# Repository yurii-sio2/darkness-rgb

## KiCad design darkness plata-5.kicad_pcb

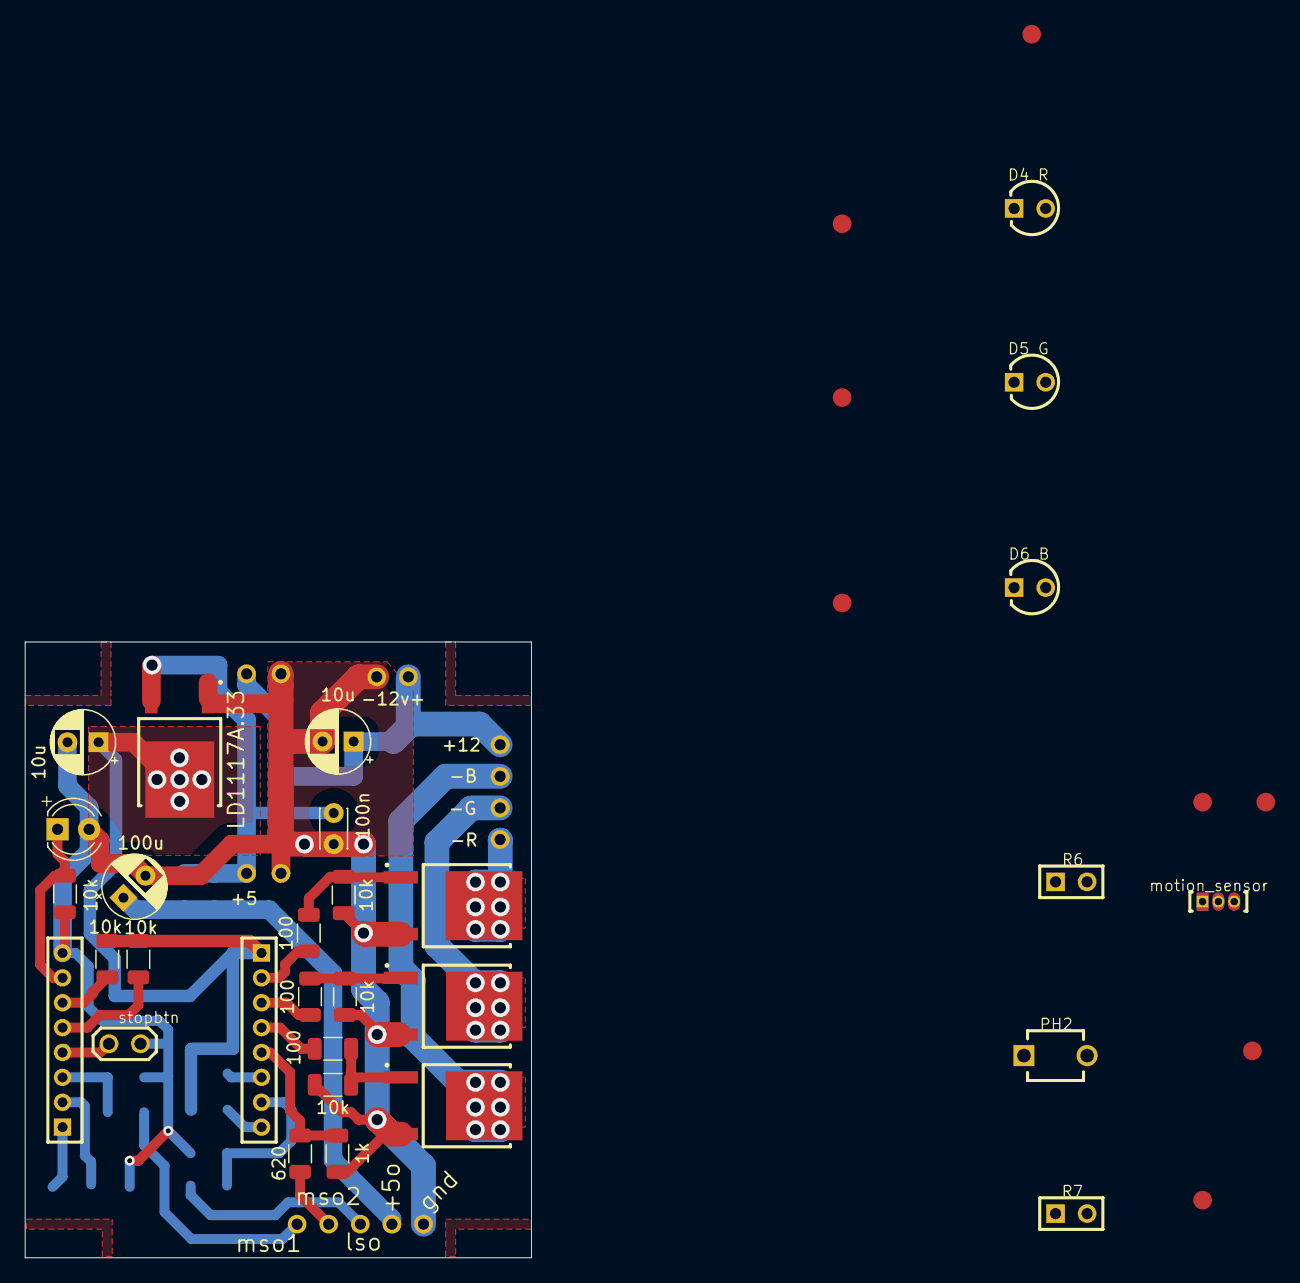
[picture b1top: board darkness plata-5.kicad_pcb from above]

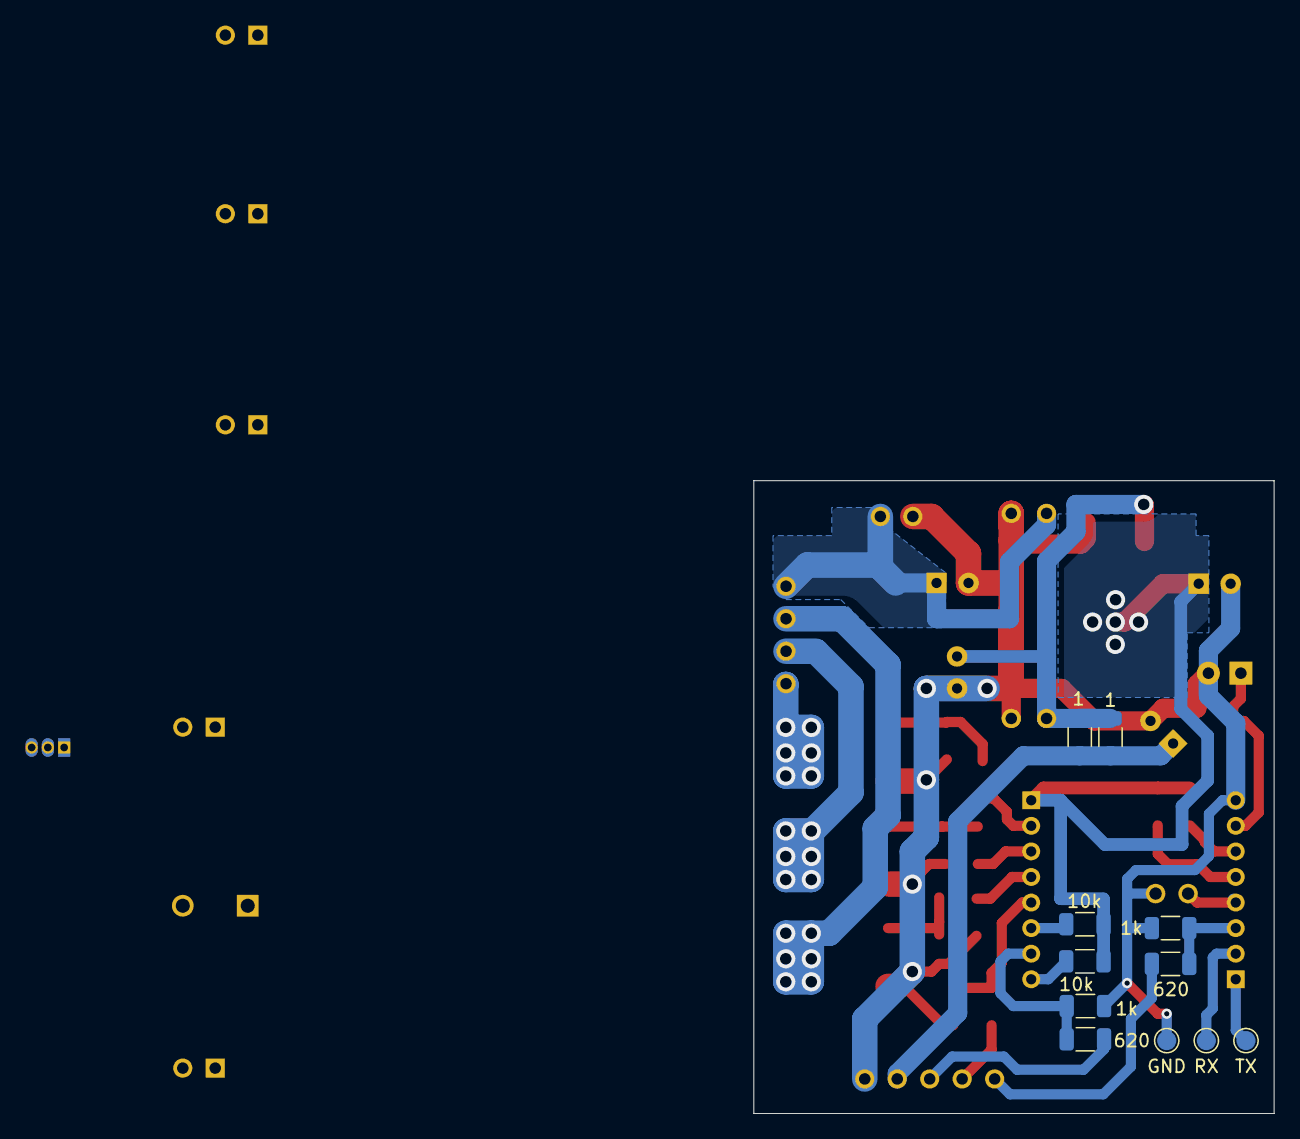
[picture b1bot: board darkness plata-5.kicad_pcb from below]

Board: 2 copper layers, 40.7 x 49.5 mm, 64 parts (11 on the bottom side), 35 nets.

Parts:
100n: 100n; C_Disc_D3.0mm_W2.0mm_P2.50mm
+3.3, +12in0: ONE CONNECTOR; One_Contact_Pin_+3.3
+12: ONE CONNECTOR; One_Contact_Pin
+12stab0: ONE CONNECTOR; One_Contact_Pin_+12stab
+rgb0: ONE CONNECTOR; One_Contact_Pin
-3.3: PAD; One_Contact_Pin_-3.3
-12: ONE CONNECTOR; One_Contact_Pin
-12in0: PAD; Pad_-12in
-B0: ONE CONNECTOR; One_Contact_Pin_-B
-G0: ONE CONNECTOR; One_Contact_Pin_-B
-R0: ONE CONNECTOR; One_Contact_Pin_-B
C1, C2: 10u; CP_Radial_D5.0mm_P2.50mm
C2#2: 100u; CP_Radial_D5.0mm_P2.50mm
D1: 4mm Round; LED_D4.0mm
D4_R0, D5_G0, D6_B0: QEC112
GND: GND; TestPoint_Pad_D1.5mm
J1, J2: 51015-0800
LIGHT_SENSOR0: ONE CONNECTOR; One_Contact_Pin_motion+3.1
PH2: 1k-150k; BP104F
Q1, Q2, Q3: P0903; TO252_50N024-09P
Q4: LD1117A.33; TO252_50N024-09P
R6: 2k; HDR-1x2
R7: 30k; HDR-1x2
R8, R9, R10#5, R11, R12, R13, R15, R17: 10k; R_1206_3216Metric
R10, R10#3, R10#6: 620; R_1206_3216Metric
R10#2, R10#4, R10#7: 1k; R_1206_3216Metric
R14, R16, R18: 100; R_1206_3216Metric
R19, R19#2: 1; R_1206_3216Metric
RX: RX; TestPoint_Pad_D1.5mm
TX: TX; TestPoint_Pad_D1.5mm
from_BLUE-0: ONE CONNECTOR; One_Contact_Pin_+12stab
from_GREEN-0: ONE CONNECTOR; One_Contact_Pin_+12stab
from_RED-0: ONE CONNECTOR; One_Contact_Pin_+12stab
motion+3.1: ONE CONNECTOR; One_Contact_Pin_motion+3.1
motion_GND1: ONE CONNECTOR; One_Contact_Pin_motion+3.1
motion_OUT1, motion_OUT2: ONE CONNECTOR; One_Contact_Pin_motion+3.1
motion_sensor0: A3058LU; SIP-3_4.58x1.55x1.27
stopbtn0: JUMPER; JMP
to+3.3v0: ONE CONNECTOR; One_Contact_Pin_+12stab
toADC0: ONE CONNECTOR; One_Contact_Pin_+12stab
toD5: ONE CONNECTOR; One_Contact_Pin_+12stab
toGND0: ONE CONNECTOR; One_Contact_Pin_+12stab

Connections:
Net_0: Q1.2, R13.2, R14.1
Net_1: 100n.2, -3.3.1, -12.1, -12in0.1, C1.2, C2.2, C2#2.2, D1.2, GND.1, J1.8, Q1.1, Q2.1, Q3.1, Q4.2, R10#2.1, R10#4.2, R10#7.1, R11.1, R13.1, R15.1, R17.1, motion_GND1.1, stopbtn0.C2
Net_2: J2.2, R14.2
Net_3: -R0.1, Q1.3
Net_4: +12.1, +12in0.1, +rgb0.1, C1.1
Net_5: Q2.2, R15.2, R16.1
Net_6: J2.3, R16.2
Net_7: J2.7, R10#3.2, R10#7.2
Net_8: -G0.1, Q2.3
Net_9: J2.4, R18.2
Net_10: Q3.2, R17.2, R18.1
Net_11: J1.3, R10#4.1, R10#6.1
Net_12: R6.1, motion_sensor0.1, to+3.3v0.1
Net_13: -B0.1, Q3.3
Net_14: motion_sensor0.3, toD5.1
Net_15: PH2.1, R6.2
Net_16: D5_G0.2, from_GREEN-0.1
Net_17: D4_R0.2, from_RED-0.1
Net_18: R7.1, motion_sensor0.2, toGND0.1
Net_19: D6_B0.2, from_BLUE-0.1
Net_20: +12stab0.1, D4_R0.1, D5_G0.1, D6_B0.1
Net_21: J1.4, stopbtn0.C1
Net_22: C2#2.1, R19.1, R19#2.1, motion+3.1.1
Net_24: PH2.2, R7.2, toADC0.1
Net_25: J2.6, R12.2
Net_26: J1.6, R9.2
Net_27: J1.5, R8.2
Net_28: J2.8, R10#5.2
Net_29: D1.1, J1.7, R11.2
Net_30: J2.5, R10.2, R10#2.2
Net_32: C2.1, J2.1, Q4.3, R8.1, R9.1, R10#5.1, R12.1
Net_33: LIGHT_SENSOR0.1, R10#3.1
Net_34: R10#6.2, motion_OUT1.1
Net_35: R10.1, motion_OUT2.1
Net_36: 100n.1, +3.3.1, Q4.1, R19.2, R19#2.2

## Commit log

2017-07-04 First commit.
2017-08-07 Updated PCB. Added program code for NodeMCU. Added pdf of the box.
2017-08-07 Moved program to the "program" folder.
2017-09-24 Update.
